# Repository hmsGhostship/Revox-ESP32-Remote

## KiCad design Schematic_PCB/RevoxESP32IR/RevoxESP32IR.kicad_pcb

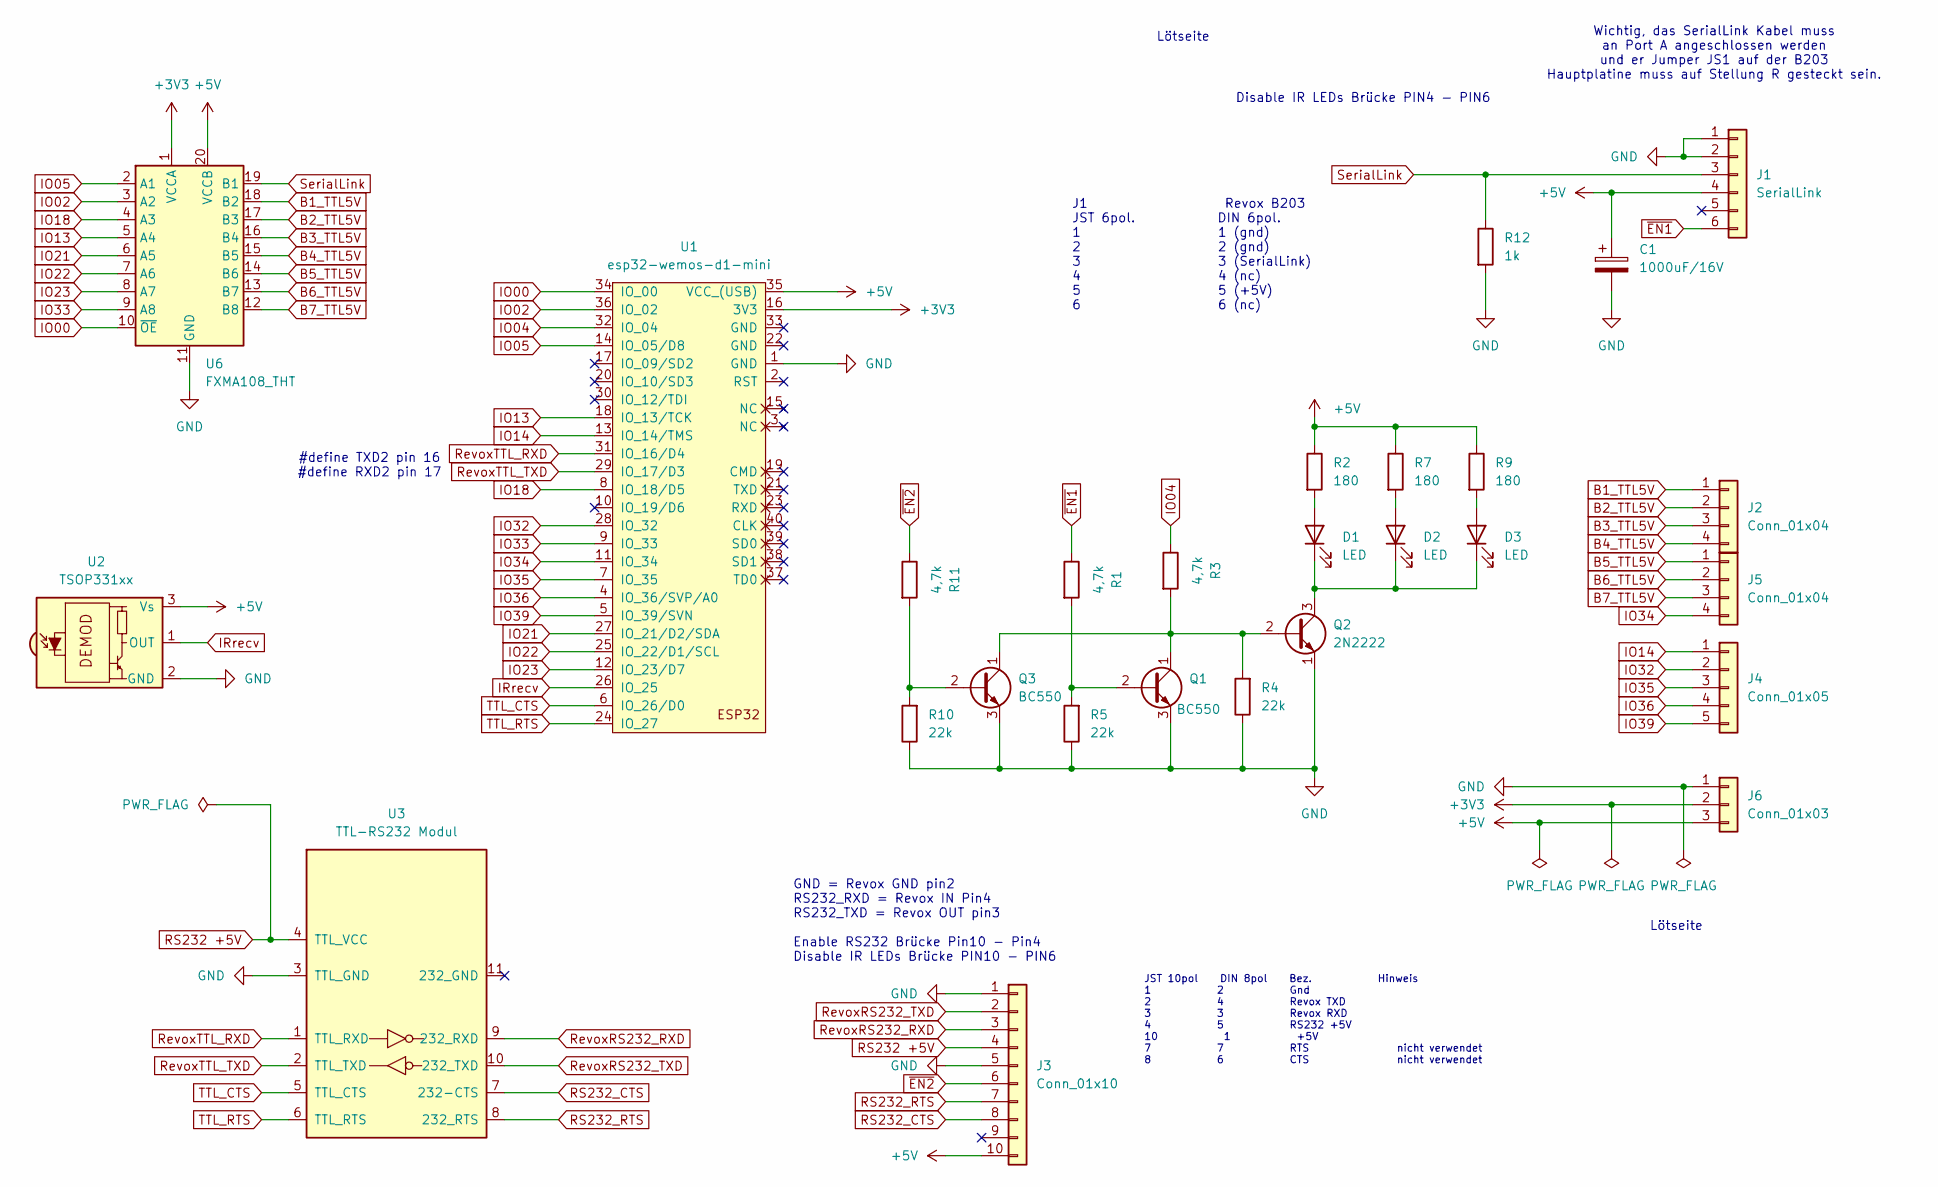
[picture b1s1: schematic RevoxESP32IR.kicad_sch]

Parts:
C1: 1000uF/16V; CP_Radial_D8.0mm_P5.00mm
D1, D2, D3: LED; LED_D3.0mm_Horizontal_O1.27mm_Z2.0mm_IRBlack
J1: SerialLink; JST_XH_B6B-XH-A_1x06_P2.50mm_Vertical
J2, J5: Conn_01x04; JST_XH_B4B-XH-A_1x04_P2.50mm_Vertical
J3: Conn_01x10; JST_XH_B10B-XH-A_1x10_P2.50mm_Vertical
J4: Conn_01x05; JST_XH_B5B-XH-A_1x05_P2.50mm_Vertical
J6: Conn_01x03; JST_XH_B3B-XH-A_1x03_P2.50mm_Vertical
Q1, Q3: BC550; TO-92_Inline
Q2: 2N2222; TO-92_Inline
R1, R3, R11: 4,7k; R_Axial_DIN0309_L9.0mm_D3.2mm_P12.70mm_Horizontal
R2, R7, R9: 180; R_Axial_DIN0309_L9.0mm_D3.2mm_P12.70mm_Horizontal
R4, R5, R10: 22k; R_Axial_DIN0309_L9.0mm_D3.2mm_P12.70mm_Horizontal
R12: 1k; R_Axial_DIN0309_L9.0mm_D3.2mm_P12.70mm_Horizontal
U1: esp32-wemos-d1-mini
U2: TSOP331xx; Vishay_MINIMOLD-3Pin
U3: TTL-RS232 Modul
U6: FXMA108_THT; DIP-20_W12.7mm_Socket_LongPads

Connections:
+3V3: J6.2, U1.16 (3V3), U6.1 (VCCA)
+5V: C1.1, J1.4, J3.10, J6.3, R2.1, R7.1, R9.1, U1.35 (VCC_(USB)), U2.3 (Vs), U6.20 (VCCB)
B1_TTL5V: J2.1, U6.18 (B2)
B2_TTL5V: J2.2, U6.17 (B3)
B3_TTL5V: J2.3, U6.16 (B4)
B4_TTL5V: J2.4, U6.15 (B5)
B5_TTL5V: J5.1, U6.14 (B6)
B6_TTL5V: J5.2, U6.13 (B7)
B7_TTL5V: J5.3, U6.12 (B8)
GND: C1.2, J1.1, J1.2, J3.1, J3.5, J6.1, Q1.3 (E), Q2.1 (E), Q3.3 (E), R4.1, R5.1, R10.1, R12.2, U1.1 (GND), U2.2 (GND), U3.3 (TTL_GND), U6.11 (GND)
IO00: U1.34 (IO_00), U6.10 (~OE)
IO02: U1.36 (IO_02), U6.3 (A2)
IO04: R3.1, U1.32 (IO_04)
IO05: U1.14 (IO_05/D8), U6.2 (A1)
IO13: U1.18 (IO_13/TCK), U6.5 (A4)
IO14: J4.1, U1.13 (IO_14/TMS)
IO18: U1.8 (IO_18/D5), U6.4 (A3)
IO21: U1.27 (IO_21/D2/SDA), U6.6 (A5)
IO22: U1.25 (IO_22/D1/SCL), U6.7 (A6)
IO23: U1.12 (IO_23/D7), U6.8 (A7)
IO32: J4.2, U1.28 (IO_32)
IO33: U1.9 (IO_33), U6.9 (A8)
IO34: J5.4, U1.11 (IO_34)
IO35: J4.3, U1.7 (IO_35)
IO36: J4.4, U1.4 (IO_36/SVP/A0)
IO39: J4.5, U1.5 (IO_39/SVN)
IRrecv: U1.26 (IO_25), U2.1 (OUT)
unnamed: D1.2 (A), R2.2
unnamed: D1.1 (K), D2.1 (K), D3.1 (K), Q2.3 (C)
unnamed: D2.2 (A), R7.2
unnamed: D3.2 (A), R9.2
unnamed: Q1.2 (B), R1.2, R5.2
unnamed: Q1.1 (C), Q2.2 (B), Q3.1 (C), R3.2, R4.2
unnamed: Q3.2 (B), R10.2, R11.2
RS232 +5V: J3.4, U3.4 (TTL_VCC)
RS232_CTS: J3.8, U3.7 (232-CTS)
RS232_RTS: J3.7, U3.8 (232_RTS)
RevoxRS232_RXD: J3.3, U3.9 (232_RXD)
RevoxRS232_TXD: J3.2, U3.10 (232_TXD)
RevoxTTL_RXD: U1.31 (IO_16/D4), U3.1 (TTL_RXD)
RevoxTTL_TXD: U1.29 (IO_17/D3), U3.2 (TTL_TXD)
SerialLink: J1.3, R12.1, U6.19 (B1)
TTL_CTS: U1.6 (IO_26/D0), U3.5 (TTL_CTS)
TTL_RTS: U1.24 (IO_27), U3.6 (TTL_RTS)
~EN1: J1.6, R1.1
~EN2: J3.6, R11.1

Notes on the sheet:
Lötseite
#define TXD2 pin 16 #define RXD2 pin 17
JST 10pol DIN 8pol Bez. Hinweis 1 2 Gnd 2 4 Revox TXD 3 3 Revox RXD 4 5 RS232 +5V 10 1 +5V 7 7 RTS nicht verwendet 8 6 CTS nicht verwendet
Wichtig, das SerialLink Kabel muss an Port A angeschlossen werden und er Jumper JS1 auf der B203 Hauptplatine muss auf Stellung R gesteckt sein.
GND = Revox GND pin2 RS232_RXD = Revox IN Pin4 RS232_TXD = Revox OUT pin3 Enable RS232 Brücke Pin10 - Pin4 Disable IR LEDs Brücke PIN10 - PIN6
Disable IR LEDs Brücke PIN4 - PIN6
J1 Revox B203 JST 6pol. DIN 6pol. 1 1 (gnd) 2 2 (gnd) 3 3 (SerialLink) 4 4 (nc) 5 5 (+5V) 6 6 (nc)

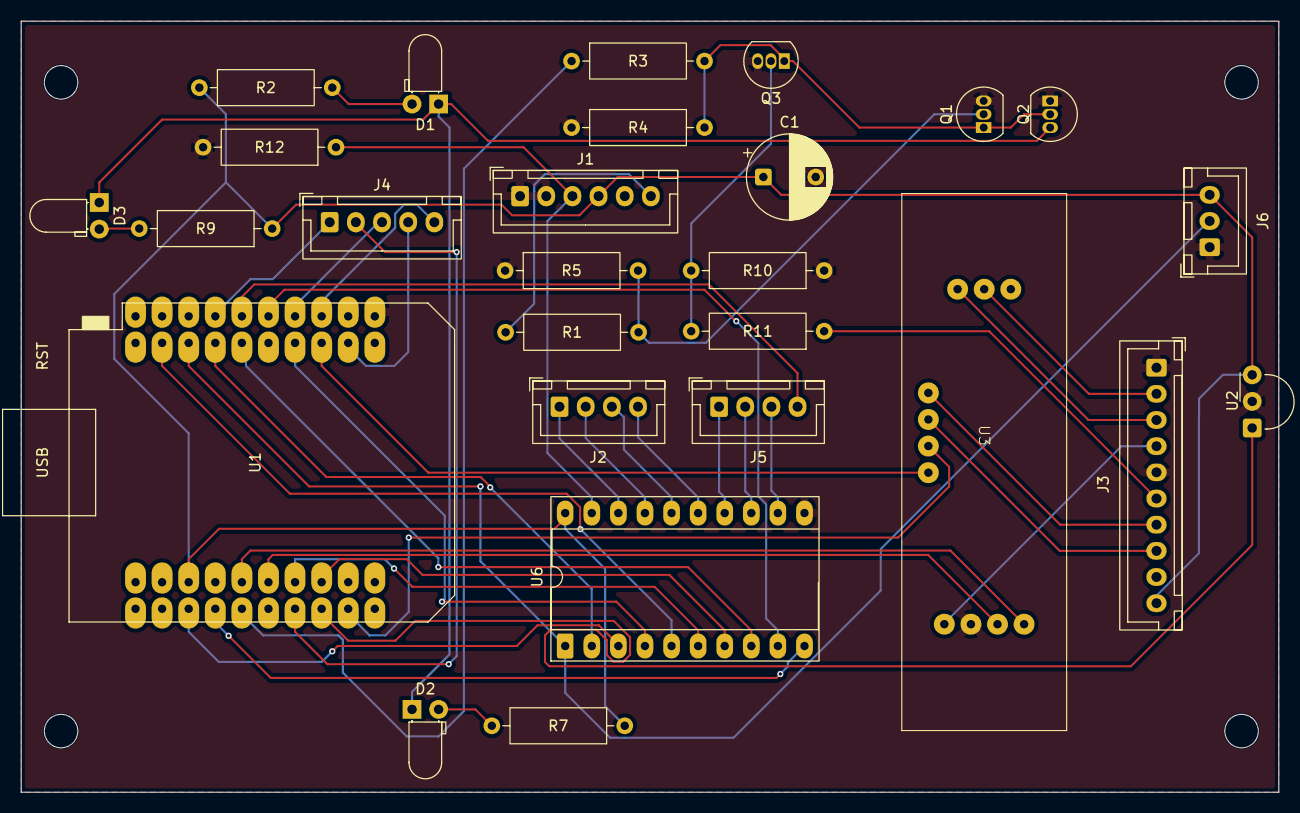
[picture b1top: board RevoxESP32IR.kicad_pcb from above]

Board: 2 copper layers, 120.1 x 73.7 mm, 31 parts (0 on the bottom side), 46 nets.

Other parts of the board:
REF1**, REF2**, REF3**, REF4**: MountingHole_3.2mm_M3

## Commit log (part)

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2026-05-08 Add new Project RevoxRemote
2026-05-09 Add Schematic and kicad_pcb
2026-05-09 New Part: Get State of CD PLayer B226
2026-05-10 Bugfix, IR send and Serial send.
2026-05-13 IR Recive geändert, Taste gedrückt und repeat.
2026-05-14 irid Variable globalisiert. Nicht benötigte Librarys entfernt.
2026-05-14 secrets.h ausgeschlossen
2026-05-14 secrets.exaple.h hinzugefügt.
2026-05-15 IR Codes für Tape1, Tape2, Amplifier, B203, Phono und CD PLayer ergänzt.
2026-05-16 Integration Revox B285 begonnen.
2026-05-17 Integration B291 Status begonnen.
2026-05-29 Bugfix wrong RXD/TXD pins.
2026-06-03 Neustart des Revox Remote Projekts
2026-06-03 wifi_config.json.example hinzugefügt.
2026-06-03 Leiterplatte neu groutet.
2026-06-03 N.V.
2026-06-03 .history gelöscht
2026-06-04 Bugfix: JavaScript Code.
2026-06-13 sendIR durch sendRevoxFrame ersetzt. Leiterplatte eneuert.
2026-06-13 Leiterplattendaten erneuert.
2026-06-13 Aufräumarbeiten.
2026-06-13 script.bak gelöscht.
2026-06-13 Aktuelle Version des Projekts hochgeladen
2026-06-13 PinDefinitionsAndMore.h und secrets.exampel.h entfernt.
2026-06-13 extra_script.bak entfernt
2026-06-14 Receiver, Amplfier und Tuner zusammengeführt.
2026-06-15 IRout zu SLout umbenannt. LabView Dateien in extra Unterordner verschoben.
2026-06-16 Phono Status zu Testzwecken aktiviert.
2026-06-19 Verbesserung bei Amplifier und Receiver, B285 erweitert.
2026-06-20 Konfiguration der IR Empfangscodes integriert.
2026-06-20 Auswahlbox für cmdFlag hinzugefügt.
2026-06-21 BiBus Prefix hinzugefügt.
2026-06-22 Umstellung der Bibus Abfrage in den SerialLink Teil.
2026-06-22 Backup der main.cpp
2026-06-22 Bibus Active wird immer angezeigt, Bibus COmmand wird komplett gesendet ausgenommen 0x Prefix.
2026-06-23 Bugfix, Statusmeldungen wurden falsch gelesen und in den HTML code eingesetzt.
2026-06-26 Bugfix: Einige verbesserungen im Javascript, 0X wurde nicht korrekt ausgeführt.
2026-06-27 Light Sleep Mode hinzugefügt.
2026-06-28 Verbesserung im HTML code. Light Version der Leiterplatte.
2026-06-29 Änderung, leeren der Variable: b203data='\0'; zu b203data = String('\0');
2026-06-29 Änderungen im serial.read, Problem mit Light sleep.
2026-06-29 Verbesserungen LightSleepMode, erkennung Tastendruck. Aufteilung verbessert, HTML Code Command-Config Seite.
